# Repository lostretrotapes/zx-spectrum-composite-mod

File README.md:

# ZX Spectrum Composite Mod Board For New Builds

This is a work in progress to make a PCB for the composite mod for the new PCBs that won't have the metal casing.

You can see the Spectrum new build series here https://www.lostretrotapes.com/building-a-new-zx-spectrum-from-all-new-parts-mostly-part-1/

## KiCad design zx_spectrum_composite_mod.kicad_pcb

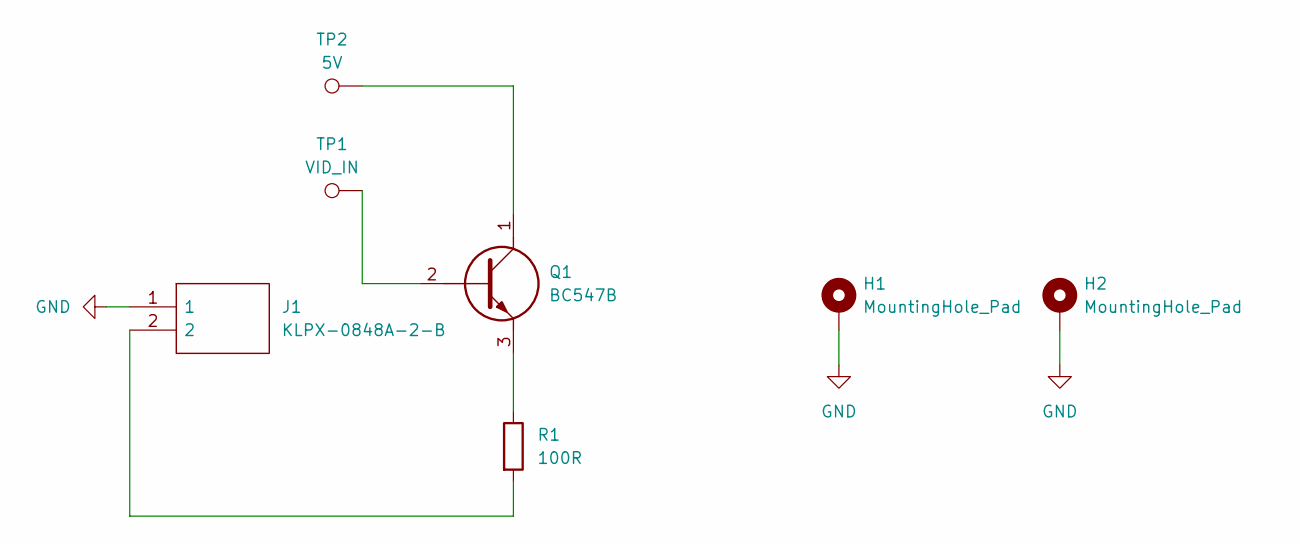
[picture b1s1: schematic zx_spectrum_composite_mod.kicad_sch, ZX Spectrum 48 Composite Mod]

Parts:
H1, H2: MountingHole_Pad; MountingHole_3.2mm_M3_Pad
J1: KLPX-0848A-2-B; KLPX0848A2B; Mouser Part Number 806-KLPX-0848A-2-B
Q1: BC547B; TO127P419X482X1041-3P; Mouser Part Number 512-BC547B
R1: 100R; R_Axial_DIN0207_L6.3mm_D2.5mm_P10.16mm_Horizontal
TP1: VID_IN; Pin_D0.7mm_L6.5mm_W1.8mm_FlatFork
TP2: 5V; Pin_D0.7mm_L6.5mm_W1.8mm_FlatFork

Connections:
GND: H1.1, H2.1, J1.1
unnamed: J1.2, R1.2
unnamed: Q1.1, TP2.1
unnamed: Q1.2, TP1.1
unnamed: Q1.3, R1.1

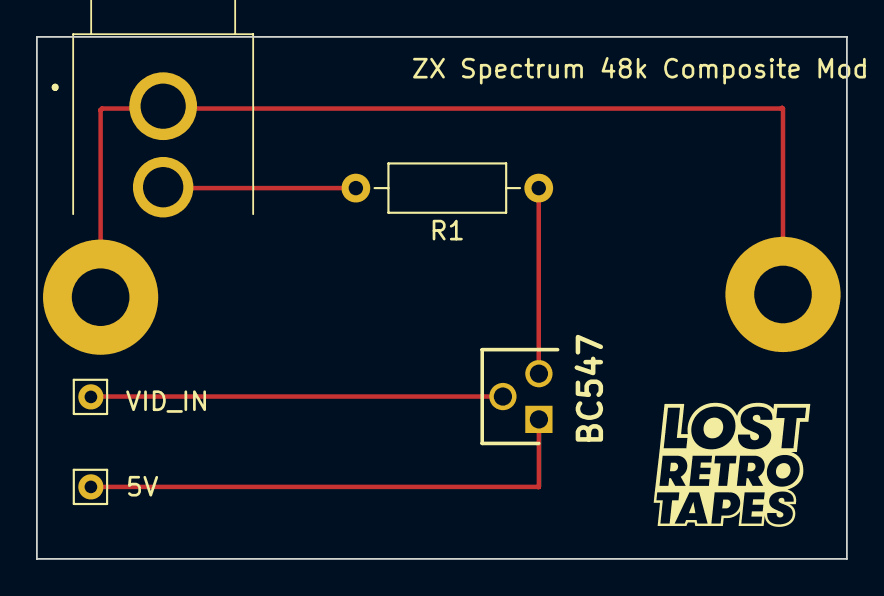
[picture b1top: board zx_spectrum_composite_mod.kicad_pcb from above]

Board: 2 copper layers, 45.0 x 29.0 mm, 7 parts (0 on the bottom side), 5 nets.

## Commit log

2023-11-24 Initial PCB
